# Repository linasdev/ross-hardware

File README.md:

# Rusty Old Smart System
This repository contains hardware for the `Rusty Old Smart System` project. 

# License
This project is licensed under the MIT License - see the [LICENSE.md](LICENSE.md) file for details.

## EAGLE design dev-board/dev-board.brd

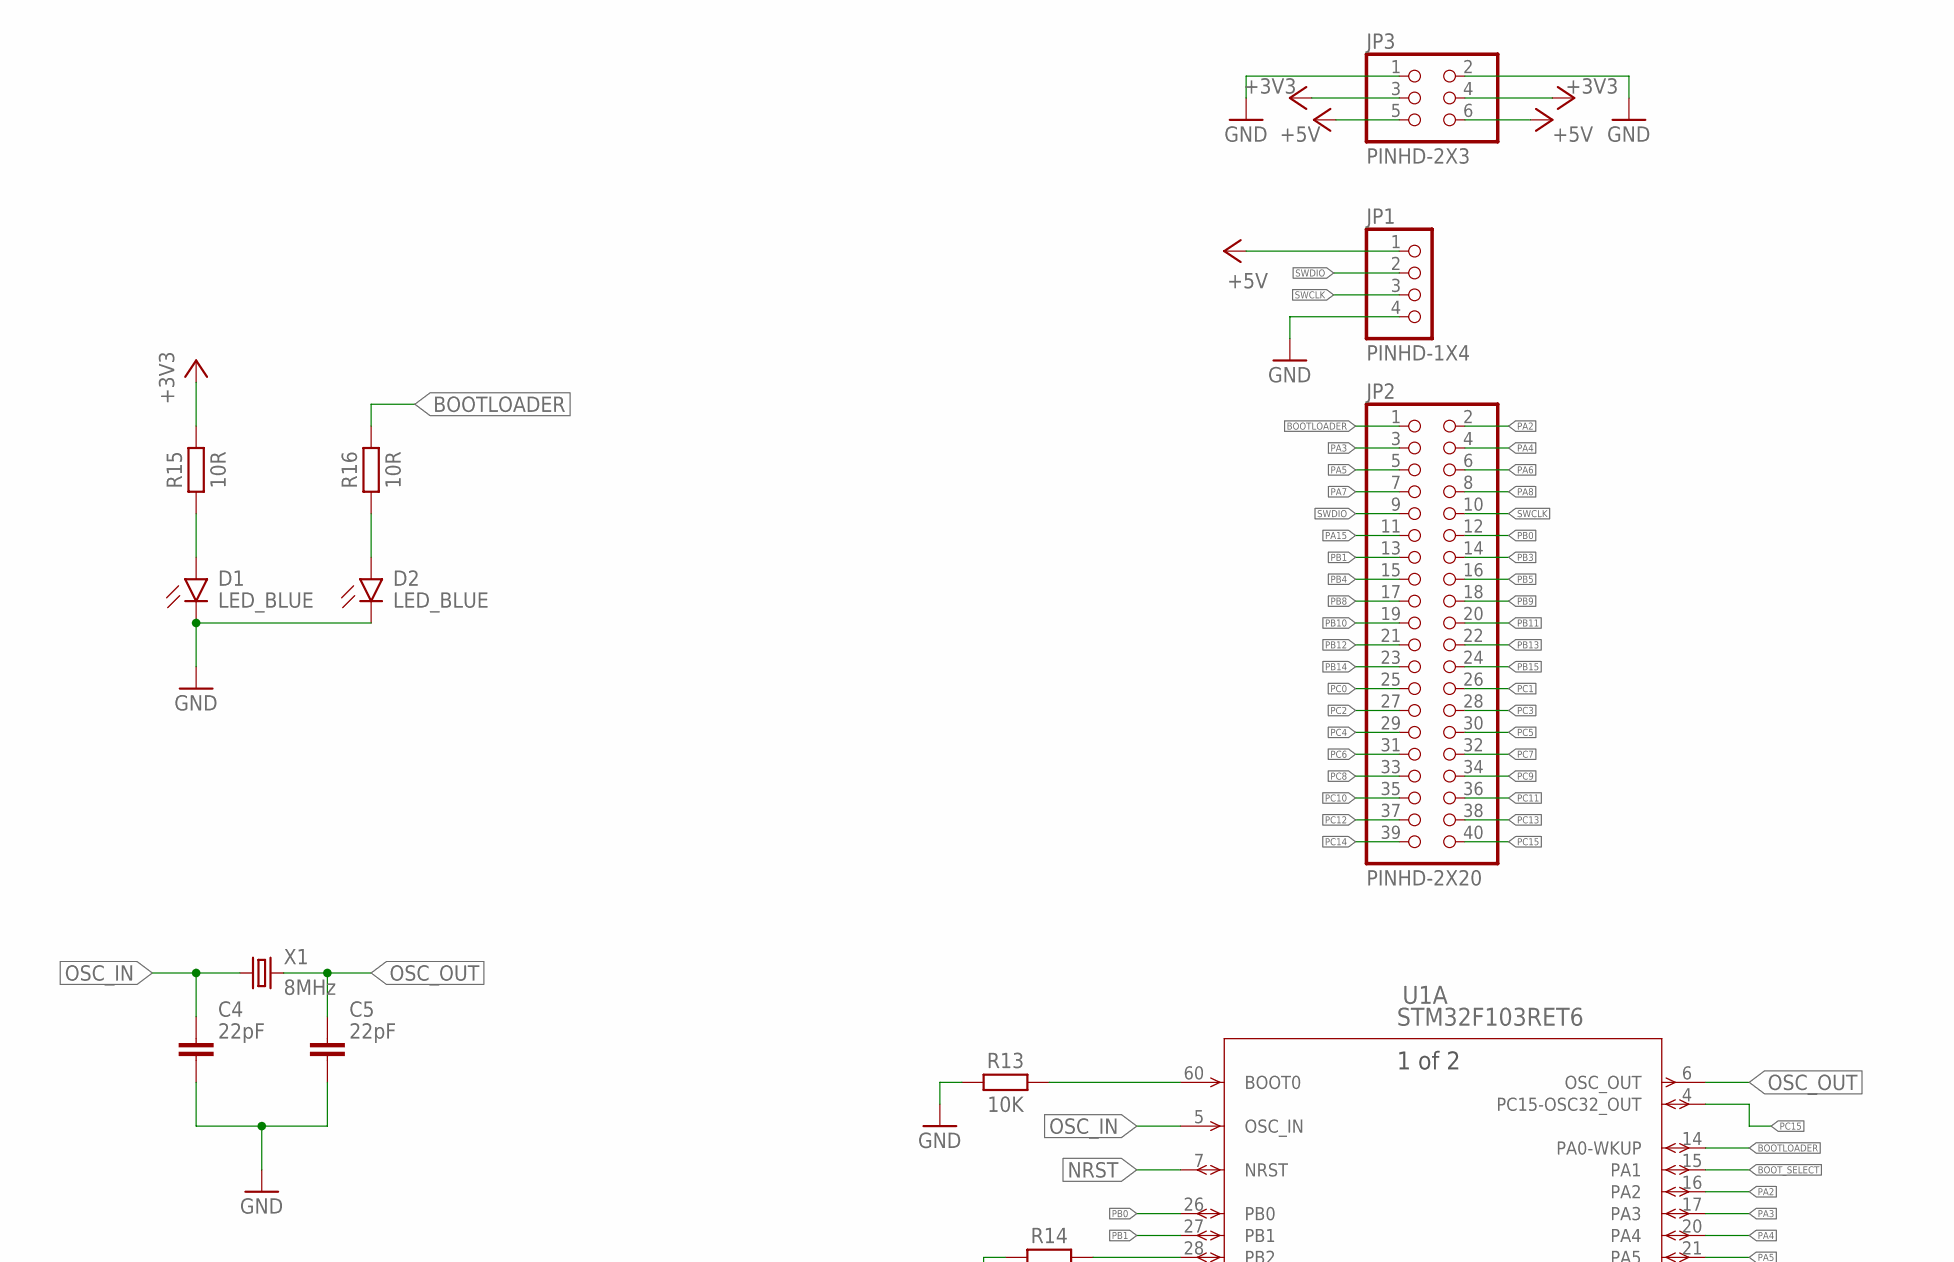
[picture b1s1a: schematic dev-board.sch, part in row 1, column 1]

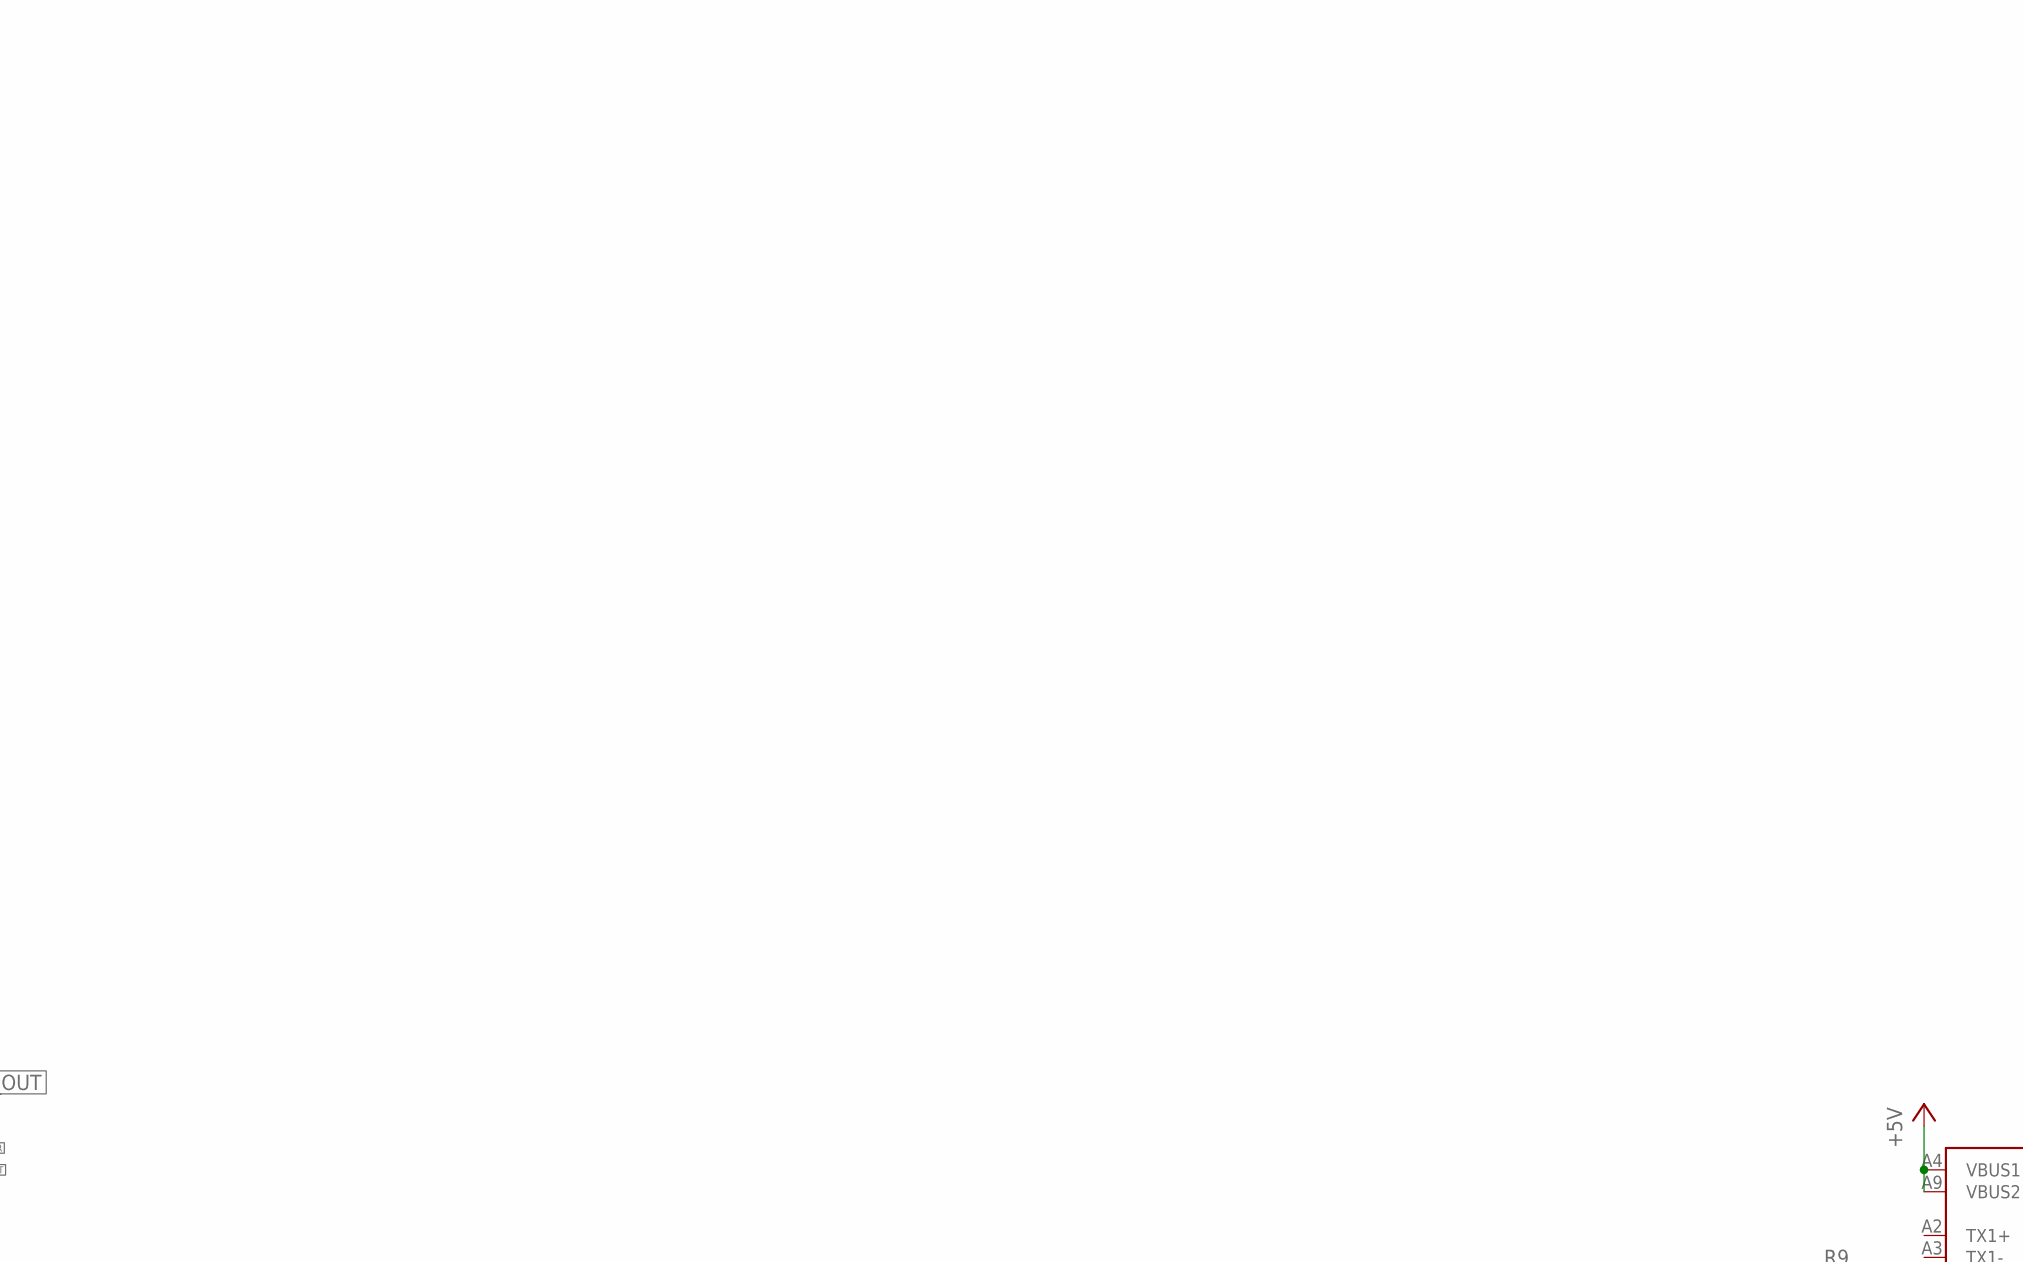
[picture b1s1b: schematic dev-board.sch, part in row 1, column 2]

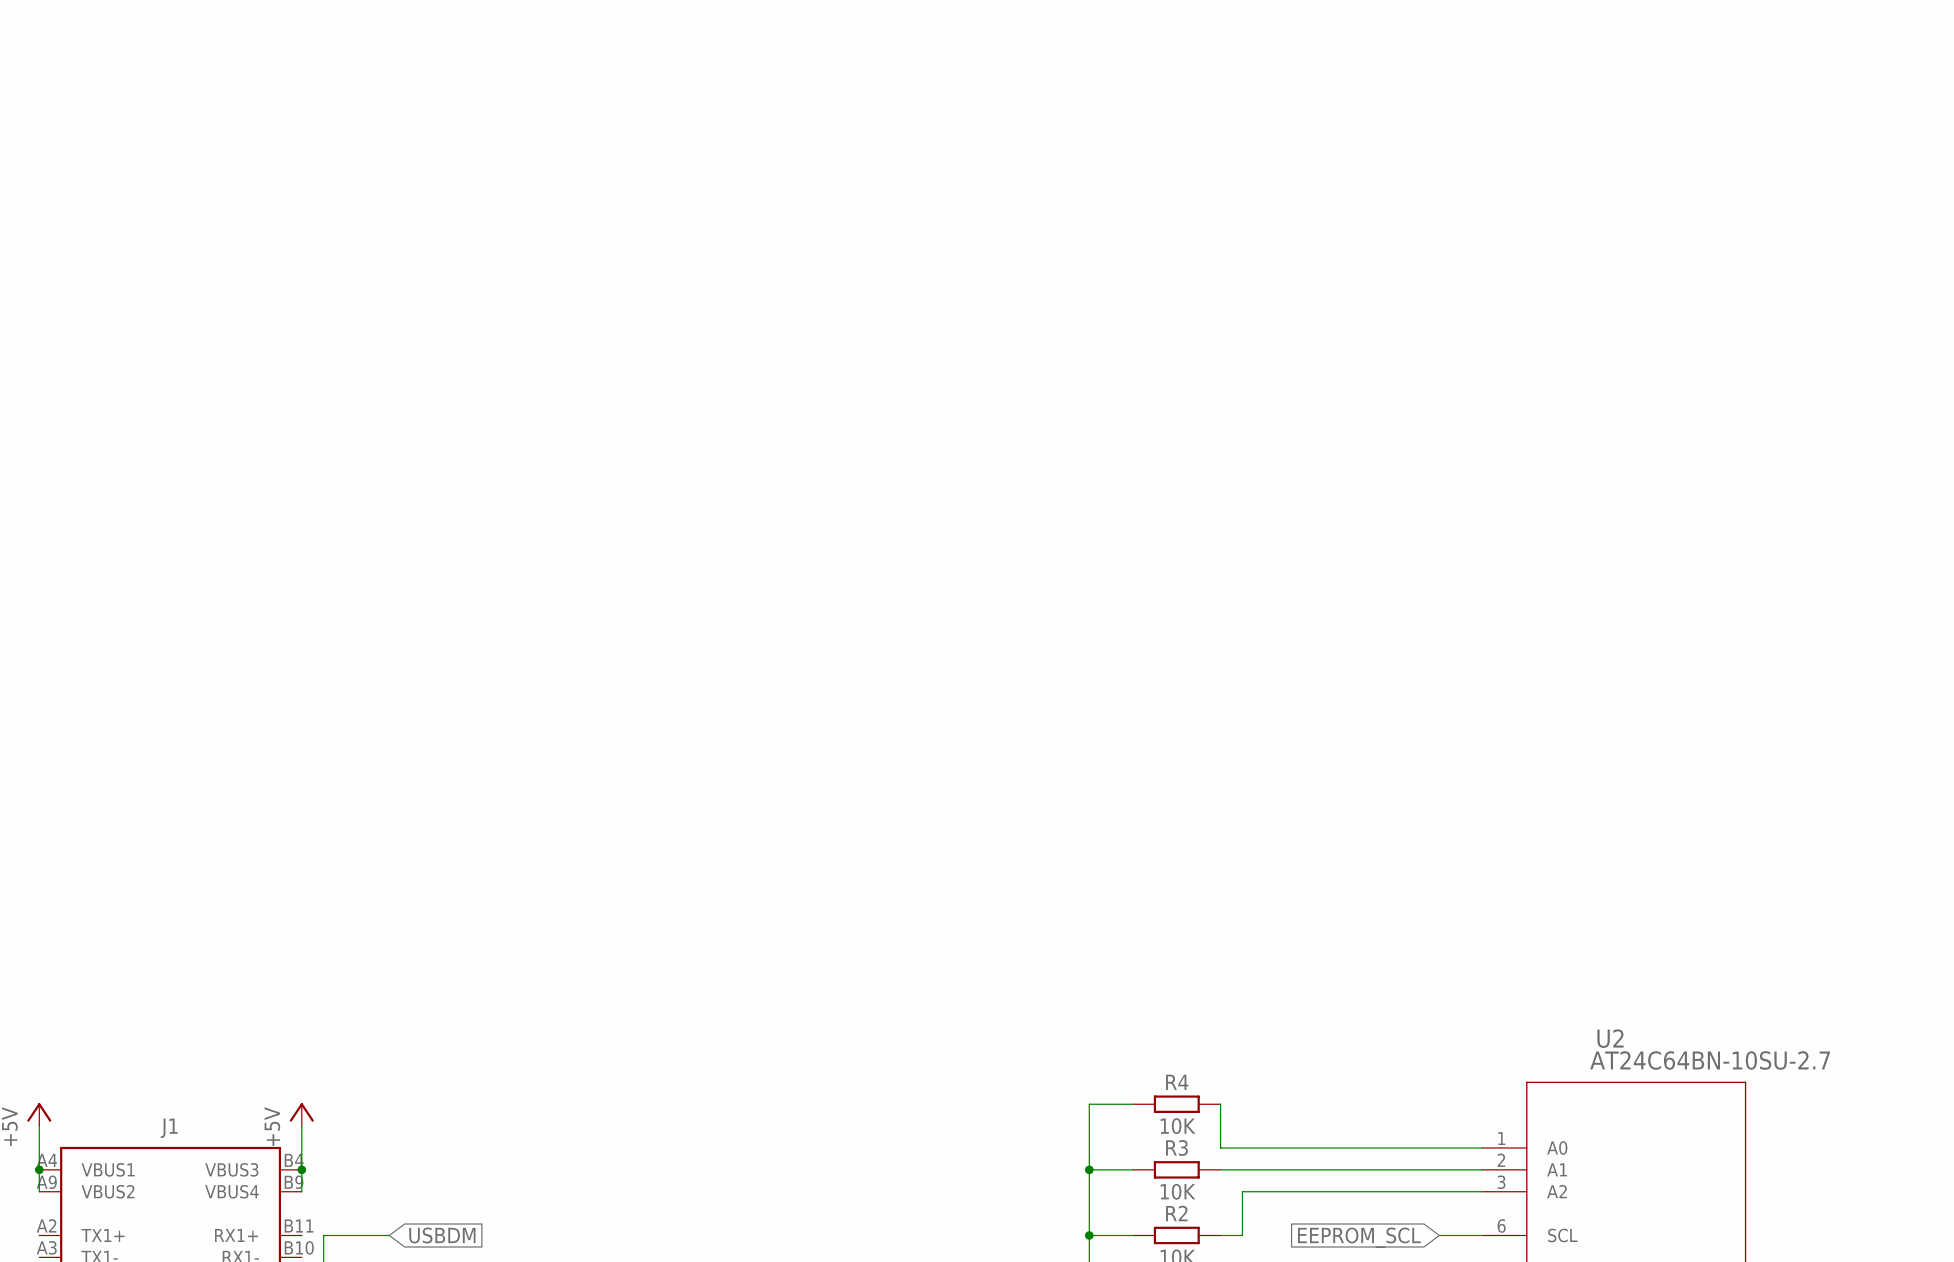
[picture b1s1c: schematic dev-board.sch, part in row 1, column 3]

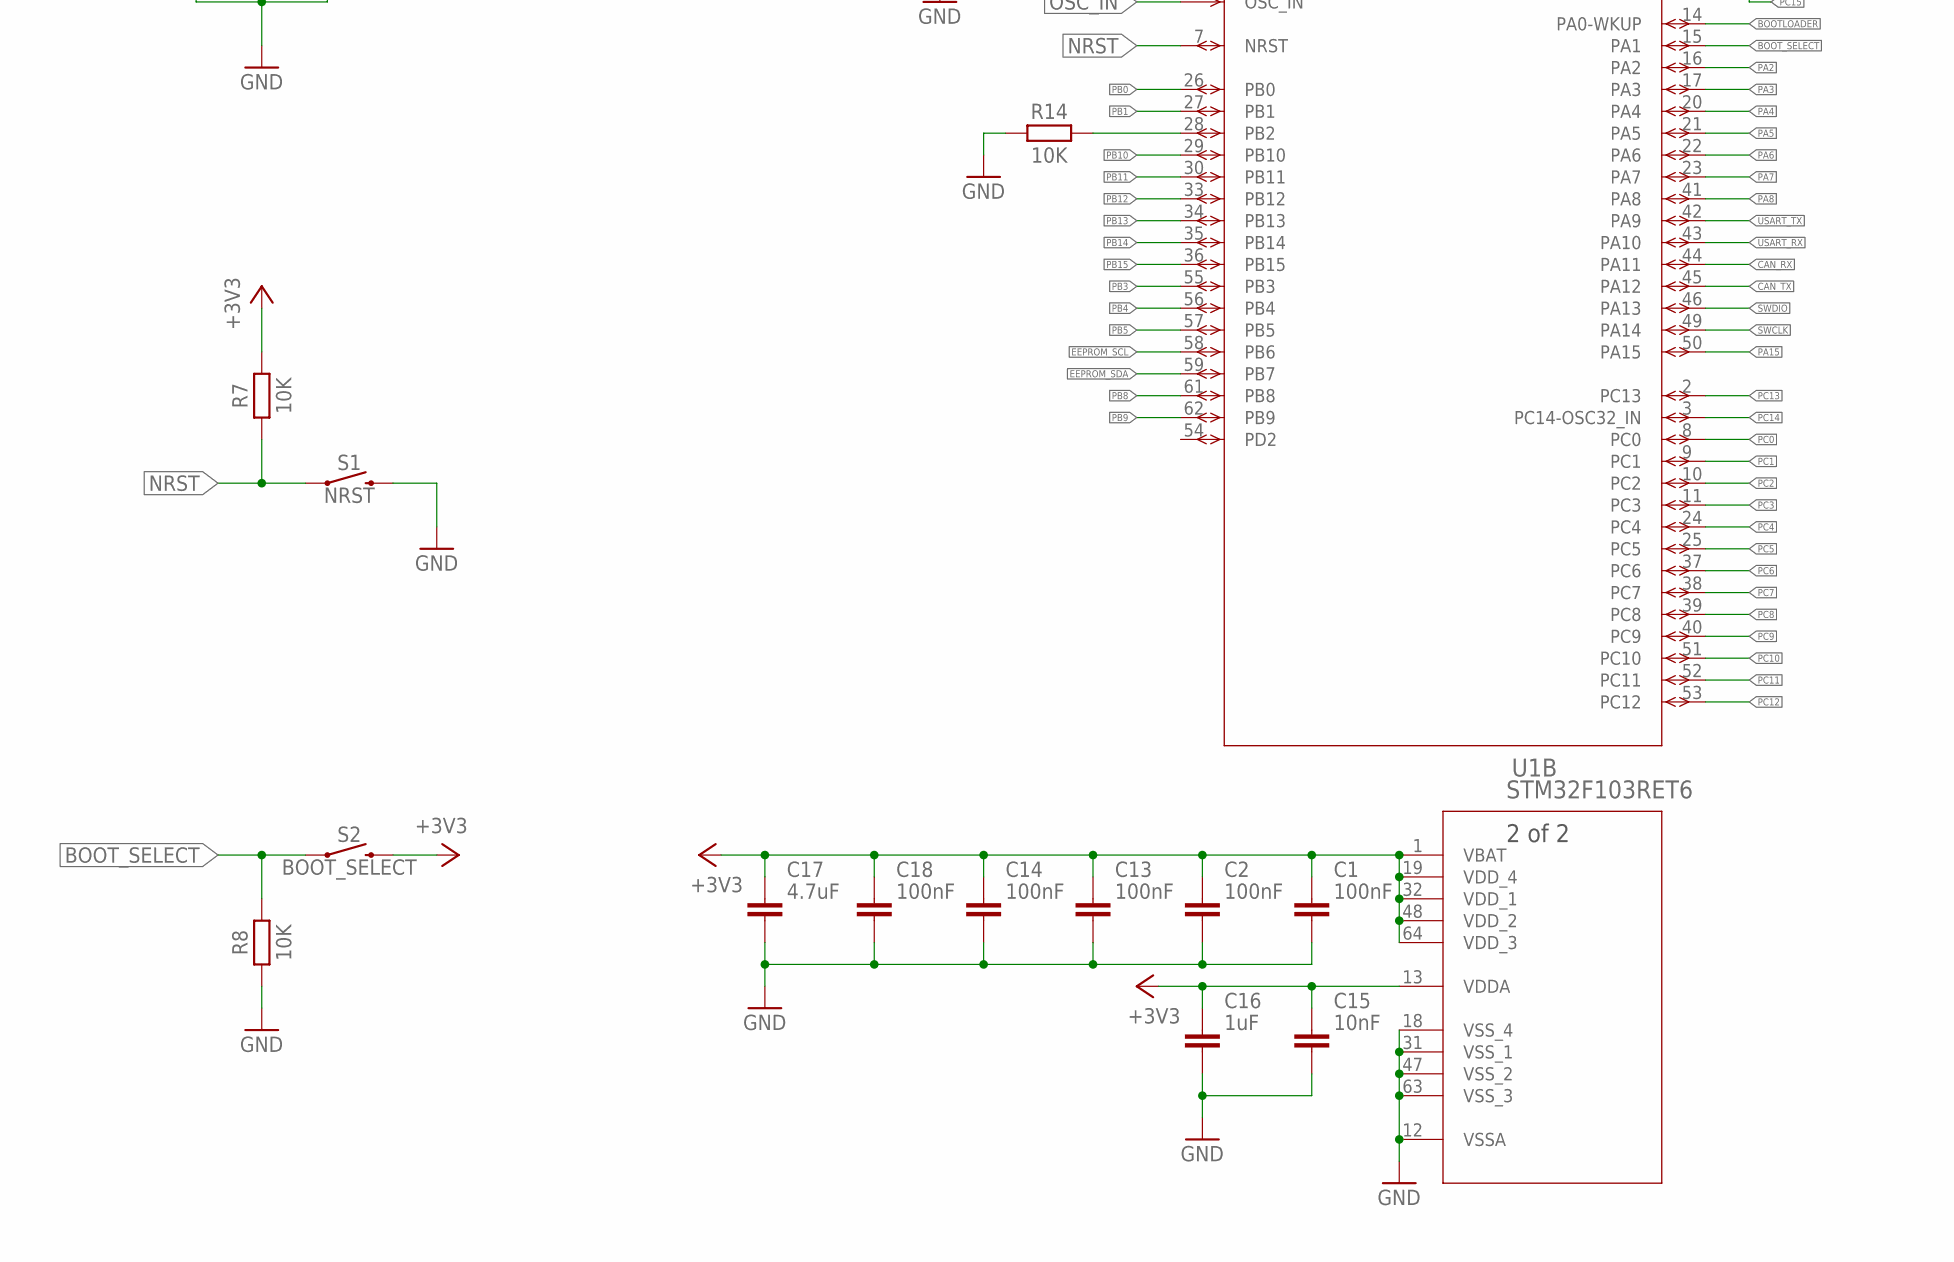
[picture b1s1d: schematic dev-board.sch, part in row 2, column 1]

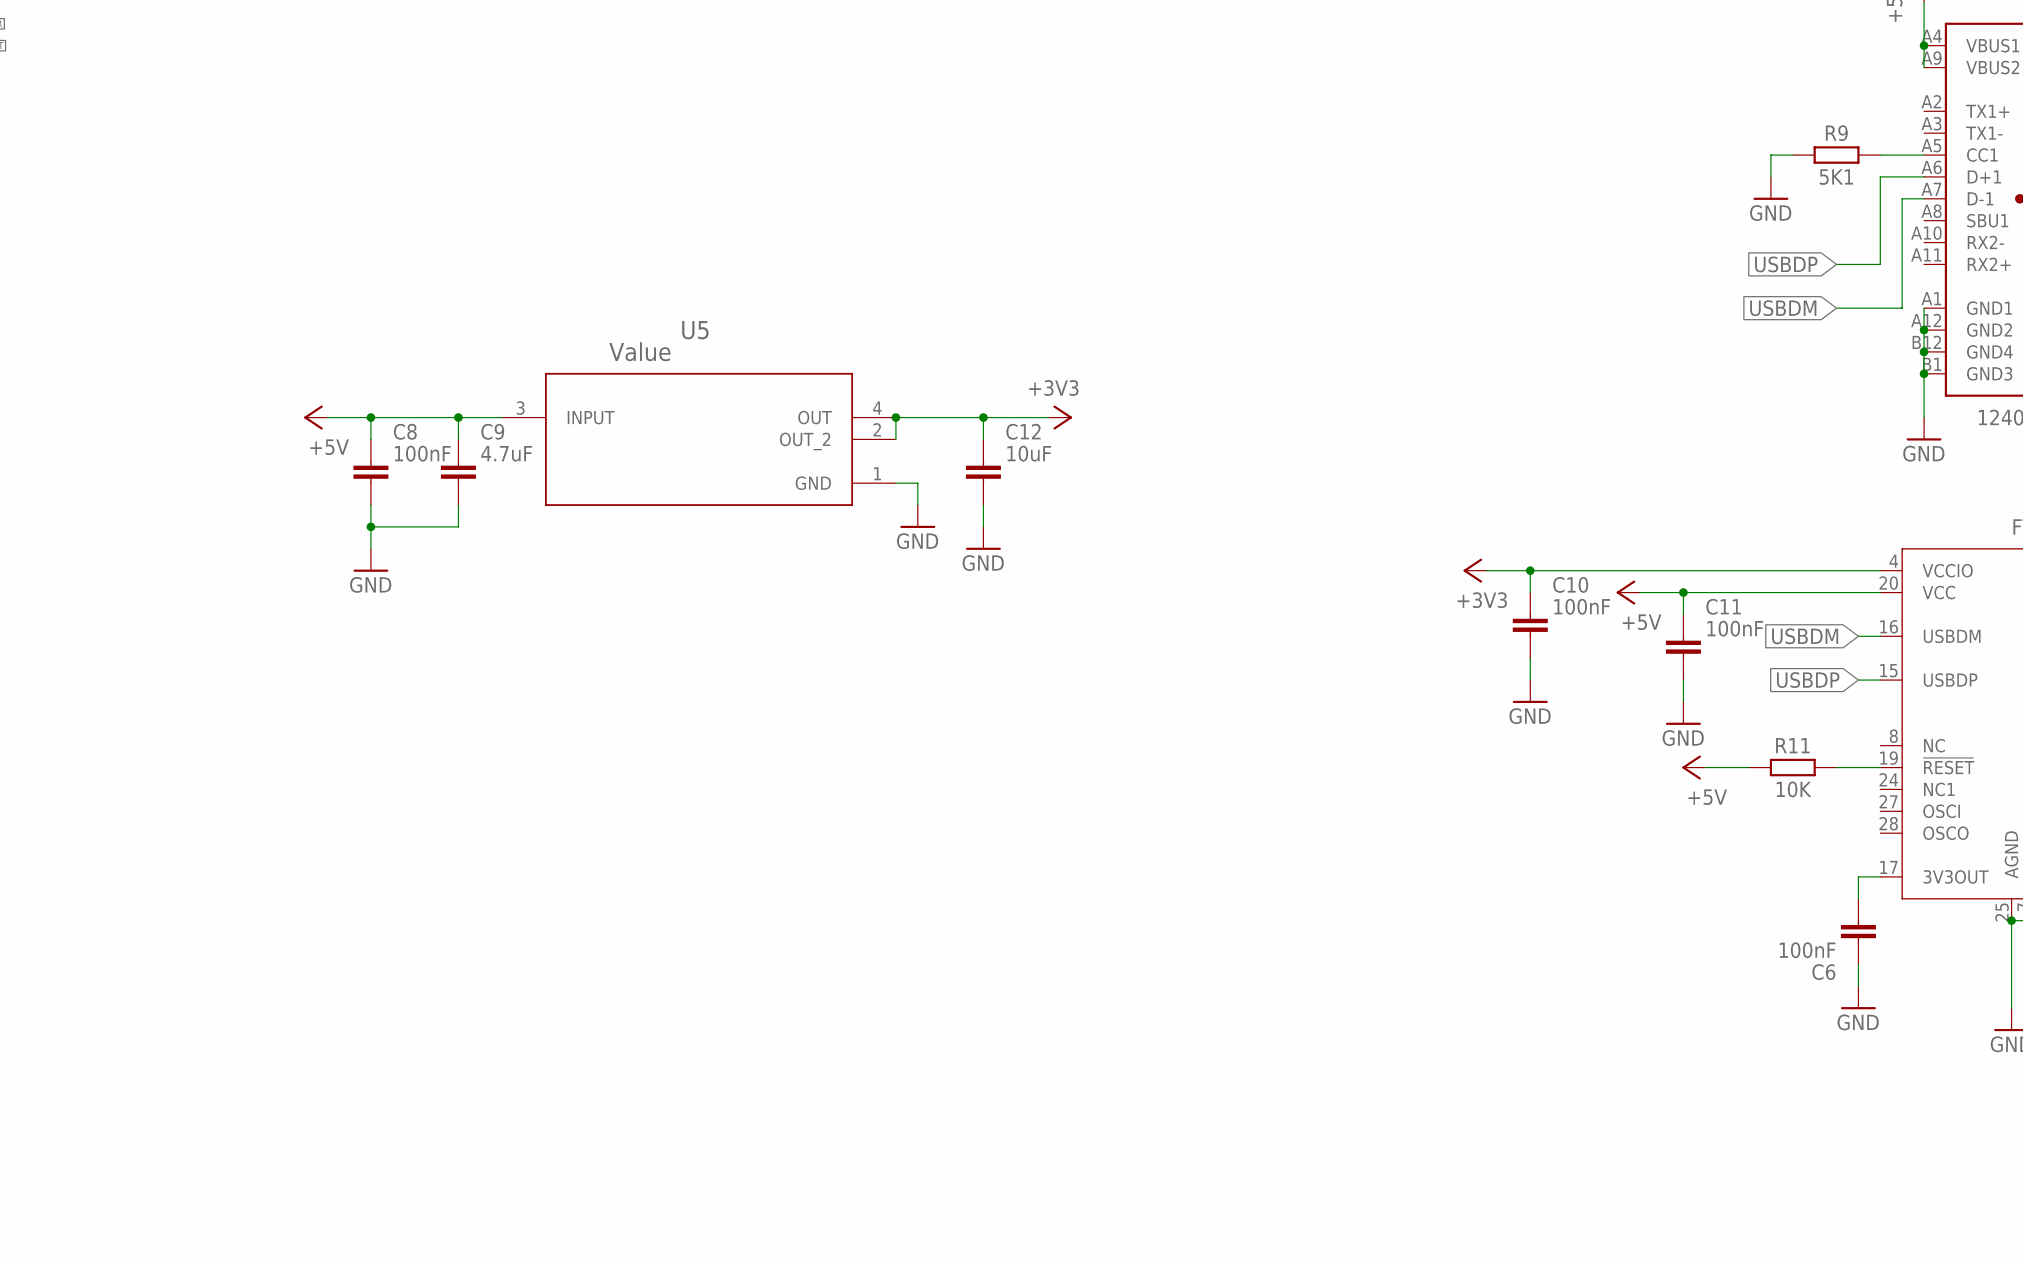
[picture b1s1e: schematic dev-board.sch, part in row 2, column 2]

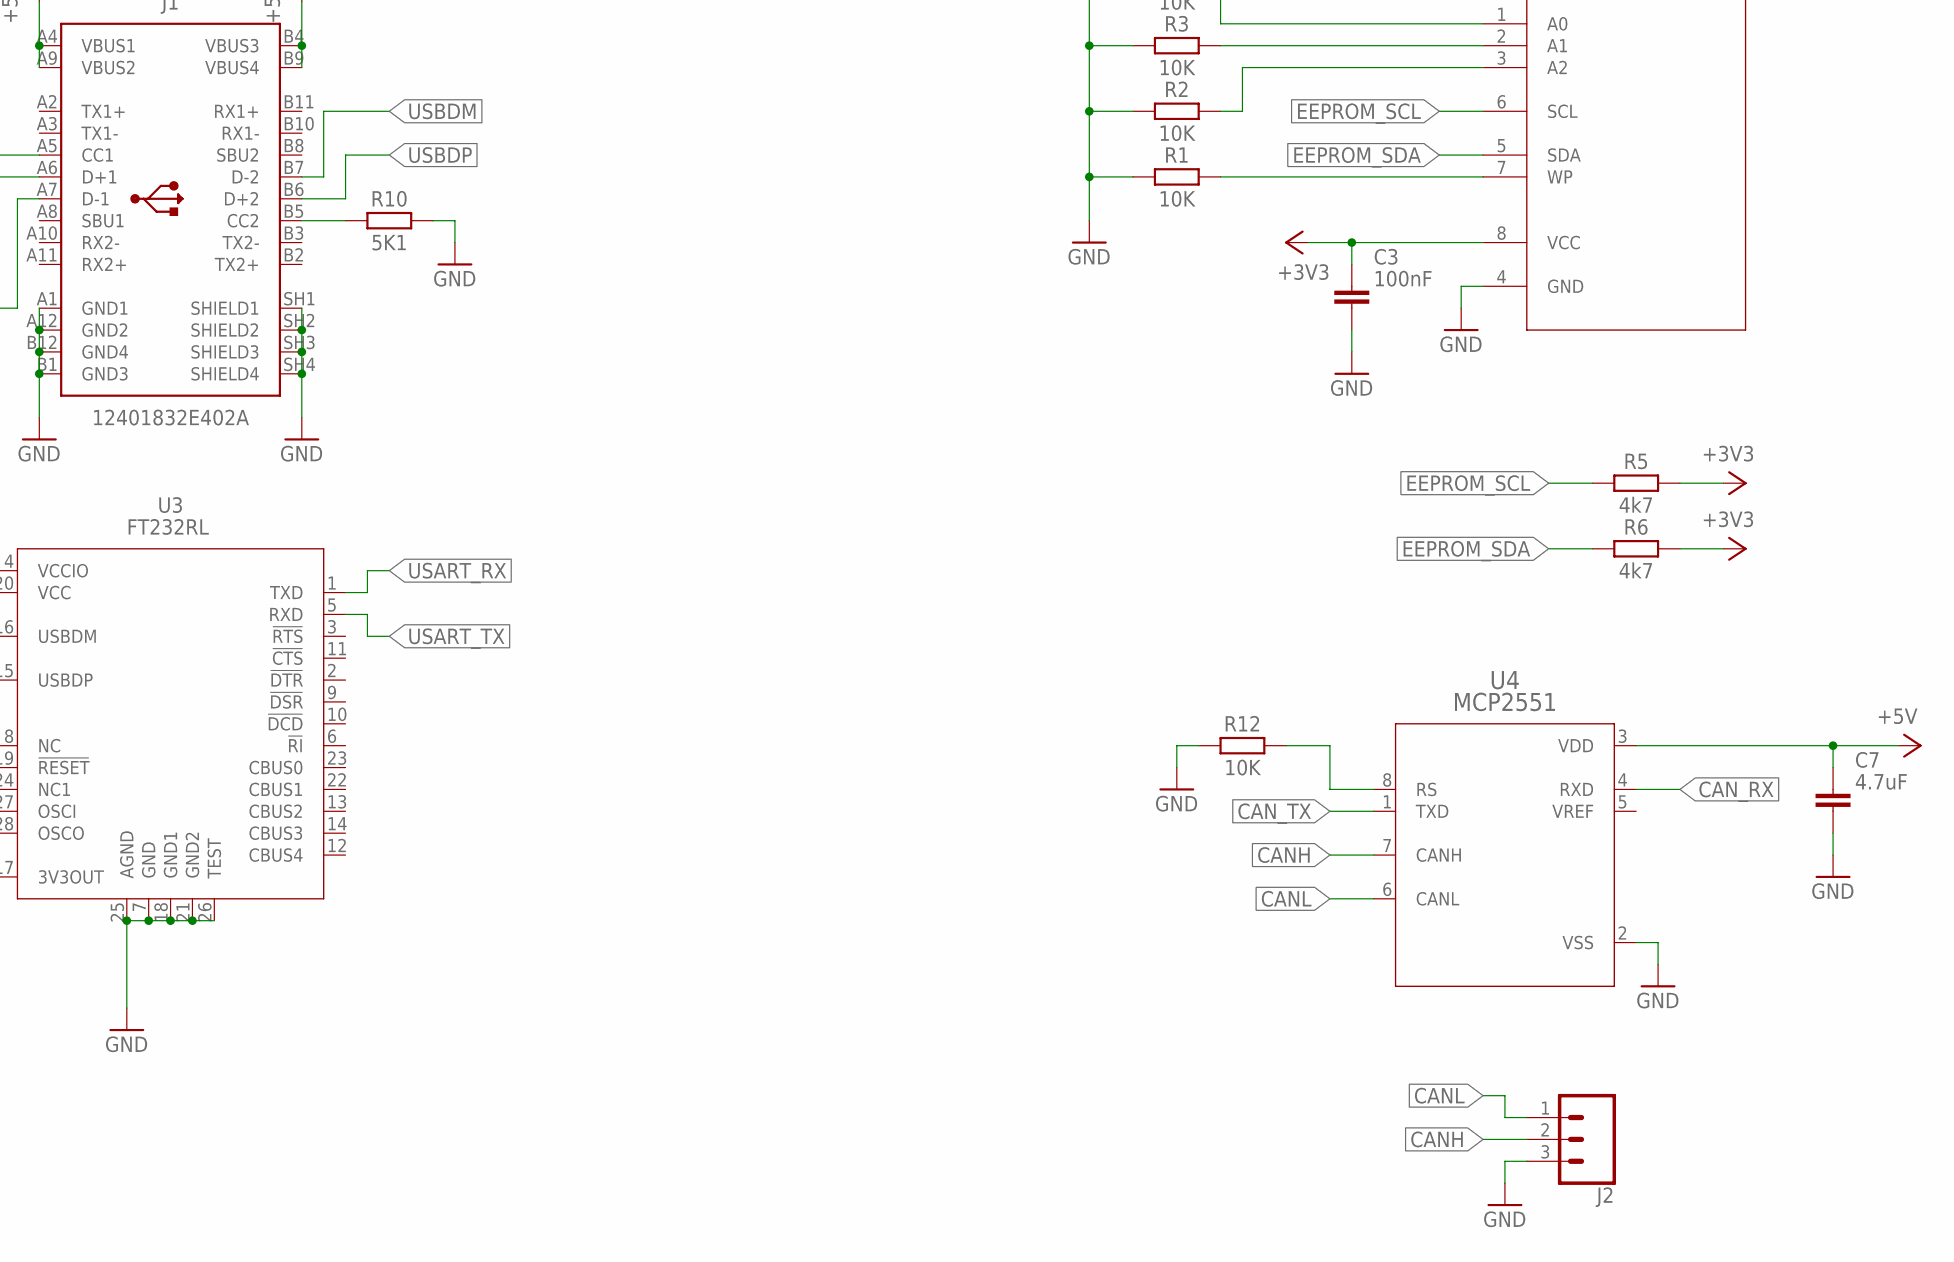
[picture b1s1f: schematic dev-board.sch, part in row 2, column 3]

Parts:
C1, C2, C3, C6, C8, C10, C11, C13, C14, C18: 100nF; CAPC2012X110
C4, C5: 22pF; CAPC2012X110
C7, C9, C17: 4.7uF; CAPC2012X110
C12: 10uF; CAPC2012X110
C15: 10nF; CAPC2012X110
C16: 1uF; CAPC2012X110
D1, D2: LED_BLUE; LEDC2012X105N_RND-R
J1: 12401832E402A
J2: CONN_03-SCREW-5MM; SCREWTERMINAL-5MM-3
JP1: PINHD-1X4; 1X04
JP2: PINHD-2X20; 2X20
JP3: PINHD-2X3; 2X03
R1, R2, R3, R4, R7, R8, R11, R12, R13, R14: 10K; RESC2012X65
R5, R6: 4k7; RESC2012X65
R9, R10: 5K1; RESC2012X65
R15, R16: 10R; RESC2012X65
S1: NRST; TACTILE_SWITCH_SMD_6.0X3.5MM
S2: BOOT_SELECT; TACTILE_SWITCH_SMD_6.0X3.5MM
U1: STM32F103RET6; LQFP64-10X10MM
U2: AT24C64BN-10SU-2.7; 8S1_ATM
U3: FT232RL; SSOP28
U4: MCP2551; SOIC127P599X175-8
U5: Value; DCY0004A_N
X1: 8MHz; HC49-4-HSMX

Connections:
+3V3: C1.1, C2.1, C3.1, C10.1, C12.1, C13.1, C14.1, C15.1, C16.1, C17.1, C18.1, JP3.3, JP3.4, R5.2, R6.2, R7.2, R15.2, S2.2, U1.1 (VBAT), U1.13 (VDDA), U1.19 (VDD_4), U1.32 (VDD_1), U1.48 (VDD_2), U1.64 (VDD_3), U2.8 (VCC), U3.4 (VCCIO), U5.2 (OUT_2), U5.4 (OUT)
+5V: C7.1, C8.1, C9.1, C11.1, J1.A4 (VBUS1), J1.A9 (VBUS2), J1.B4 (VBUS3), J1.B9 (VBUS4), JP1.1, JP3.5, JP3.6, R11.1, U3.20 (VCC), U4.3 (VDD), U5.3 (INPUT)
BOOTLOADER: JP2.1, R16.2, U1.14 (PA0-WKUP)
BOOT_SELECT: R8.2, S2.1, U1.15 (PA1)
CANH: J2.2, U4.7 (CANH)
CANL: J2.1, U4.6 (CANL)
CAN_RX: U1.44 (PA11), U4.4 (RXD)
CAN_TX: U1.45 (PA12), U4.1 (TXD)
EEPROM_SCL: R5.1, U1.58 (PB6), U2.6 (SCL)
EEPROM_SDA: R6.1, U1.59 (PB7), U2.5 (SDA)
GND: C1.2, C2.2, C3.2, C4.2, C5.2, C6.1, C7.2, C8.2, C9.2, C10.2, C11.2, C12.2, C13.2, C14.2, C15.2, C16.2, C17.2, C18.2, D1.C, D2.C, J1.A1 (GND1), J1.A12 (GND2), J1.B1 (GND3), J1.B12 (GND4), J1.SH1 (SHIELD1), J1.SH2 (SHIELD2), J1.SH3 (SHIELD3), J1.SH4 (SHIELD4), J2.3, JP1.4, JP3.1, JP3.2, R1.1, R2.1, R3.1, R4.1, R8.1, R9.1, R10.2, R12.1, R13.1, R14.1, S1.2, U1.12 (VSSA), U1.18 (VSS_4), U1.31 (VSS_1), U1.47 (VSS_2), U1.63 (VSS_3), U2.4 (GND), U3.7 (GND), U3.18 (GND1), U3.21 (GND2), U3.25 (AGND), U3.26 (TEST), U4.2 (VSS), U5.1 (GND)
unnamed: R2.2, U2.3 (A2)
unnamed: R3.2, U2.2 (A1)
unnamed: R4.2, U2.1 (A0)
unnamed: R1.2, U2.7 (WP)
unnamed: R12.2, U4.8 (RS)
unnamed: R14.2, U1.28 (PB2)
unnamed: D1.A, R15.1
unnamed: D2.A, R16.1
unnamed: R13.2, U1.60 (BOOT0)
unnamed: C6.2, U3.17 (3V3OUT)
unnamed: J1.A5 (CC1), R9.2
unnamed: R11.2, U3.19 (!RESET)
unnamed: J1.B5 (CC2), R10.1
NRST: R7.1, S1.1, U1.7 (NRST)
OSC_IN: C4.1, U1.5 (OSC_IN), X1.1
OSC_OUT: C5.1, U1.6 (OSC_OUT), X1.2
PA2: JP2.2, U1.16 (PA2)
PA3: JP2.3, U1.17 (PA3)
PA4: JP2.4, U1.20 (PA4)
PA5: JP2.5, U1.21 (PA5)
PA6: JP2.6, U1.22 (PA6)
PA7: JP2.7, U1.23 (PA7)
PA8: JP2.8, U1.41 (PA8)
PA15: JP2.11, U1.50 (PA15)
PB0: JP2.12, U1.26 (PB0)
PB1: JP2.13, U1.27 (PB1)
PB3: JP2.14, U1.55 (PB3)
PB4: JP2.15, U1.56 (PB4)
PB5: JP2.16, U1.57 (PB5)
PB8: JP2.17, U1.61 (PB8)
PB9: JP2.18, U1.62 (PB9)
PB10: JP2.19, U1.29 (PB10)
PB11: JP2.20, U1.30 (PB11)
PB12: JP2.21, U1.33 (PB12)
PB13: JP2.22, U1.34 (PB13)
PB14: JP2.23, U1.35 (PB14)
PB15: JP2.24, U1.36 (PB15)
PC0: JP2.25, U1.8 (PC0)
PC1: JP2.26, U1.9 (PC1)
PC2: JP2.27, U1.10 (PC2)
PC3: JP2.28, U1.11 (PC3)
PC4: JP2.29, U1.24 (PC4)
PC5: JP2.30, U1.25 (PC5)
PC6: JP2.31, U1.37 (PC6)
PC7: JP2.32, U1.38 (PC7)
PC8: JP2.33, U1.39 (PC8)
PC9: JP2.34, U1.40 (PC9)
PC10: JP2.35, U1.51 (PC10)
PC11: JP2.36, U1.52 (PC11)
PC12: JP2.37, U1.53 (PC12)
PC13: JP2.38, U1.2 (PC13)
PC14: JP2.39, U1.3 (PC14-OSC32_IN)
PC15: JP2.40, U1.4 (PC15-OSC32_OUT)
SWCLK: JP1.3, JP2.10, U1.49 (PA14)
SWDIO: JP1.2, JP2.9, U1.46 (PA13)
USART_RX: U1.43 (PA10), U3.1 (TXD)
USART_TX: U1.42 (PA9), U3.5 (RXD)
USBDM: J1.A7 (D-1), J1.B7 (D-2), U3.16 (USBDM)
USBDP: J1.A6 (D+1), J1.B6 (D+2), U3.15 (USBDP)

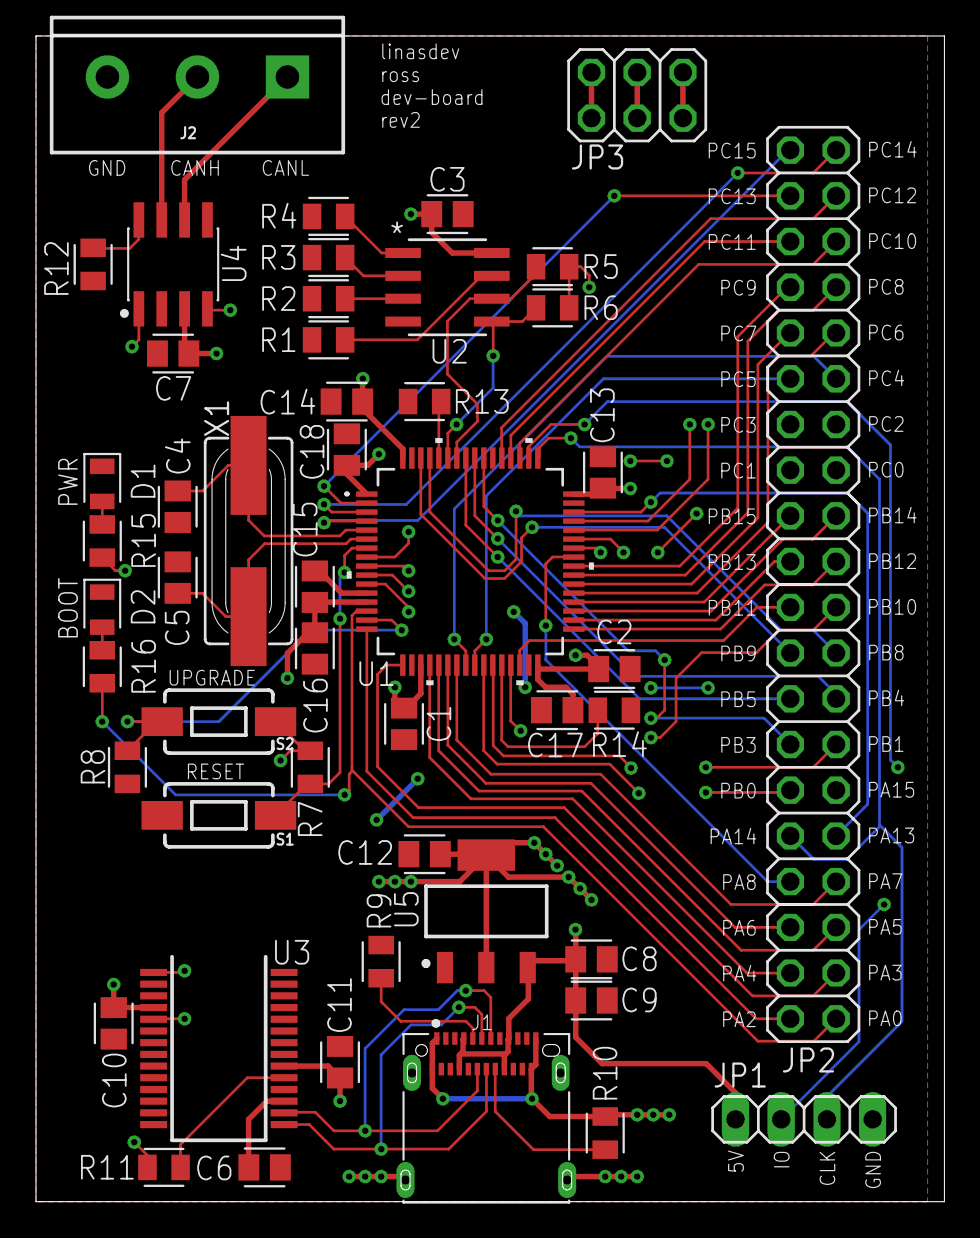
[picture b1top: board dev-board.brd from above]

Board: 4 copper layers, 50.5 x 64.8 mm, 49 parts (0 on the bottom side), 70 nets.

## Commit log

2021-11-22 Create project structure
2021-11-22 Add programmer hardware
2021-11-23 Add development board schematic and board design
2021-11-23 Switch to a 4 layer pcb
2021-11-24 Finish dev-board layout
2021-11-24 Remove programmer board
2021-11-24 Fix dev-board silkscreen
2021-11-26 Fix some issues with the dev-board design
2021-11-26 Add more info to the silkscreen (dev-board)
2021-11-26 Fix 5V plane problem in dev-board pcb design
2021-11-26 Improve dev-board design further
2021-11-26 Remove leftover stuff
2021-11-27 Improve dev-board top layer ground plane
2021-11-30 Add dev-board gerber files
2021-12-22 Remove gerber files (add them to release later)
2021-12-22 Clean up dev-board schematic
2021-12-23 Proper decoupling caps for stm32
2021-12-23 Proper bulk cap for regulator
2021-12-23 Bulkier MCP2551 decoupling cap
2021-12-23 Redesign of dev-board USB connector area
2021-12-23 Fix stm32 decoupling caps in dev-board pcb design
2021-12-23 Put C12 bulk cap closer to regulator and provide more stitching vias
2021-12-23 Move crystal oscillator closer to the stm32
2021-12-23 Add rev2 label to dev-board pcb
2021-12-23 Fix up dev-board mcp2551 pcb area
2021-12-23 Remove designator labels around regulator in dev-boarc pcb
2021-12-23 Move things around
2021-12-23 Move usart traces closer
2021-12-23 Move R9 to the opposite side of the connector
2021-12-23 Move 5V trace to the right a bit
2021-12-23 Move C6 closer to the pin
2021-12-23 Better ground stitching
2021-12-23 Connect GND planes
2021-12-23 Touch things up
2021-12-24 Better stitching
2021-12-24 Add silkscreen button labels
2021-12-24 Improve silkscreen clarity around the header
2021-12-24 Cosmetic change
2022-03-10 Add leds
2022-03-10 Add breakout for various voltages

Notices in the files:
parts and their libraries:
SparkFun-Connectors: Licensing: Creative Commons ShareAlike 4.0 International - https://creativecommons.org/licenses/by-sa/4.0
COPYRIGHT: Copyright (C) 2018 Accelerated Designs. All rights reserved
